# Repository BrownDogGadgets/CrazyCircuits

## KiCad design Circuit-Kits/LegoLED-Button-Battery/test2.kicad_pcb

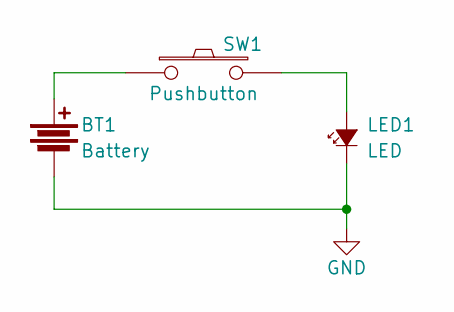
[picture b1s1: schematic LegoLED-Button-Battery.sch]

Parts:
BT1: Battery; CR2032-3x3-NO-ROTATE
LED1: LED; LED-5MMD-2.5MMP-2x2
SW1: Pushbutton; BUTTON-1x3-TH-OMRON-B3F-1XXX

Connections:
GND: BT1.GND, LED1.-
unnamed: BT1.+, SW1.1
unnamed: LED1.+, SW1.2

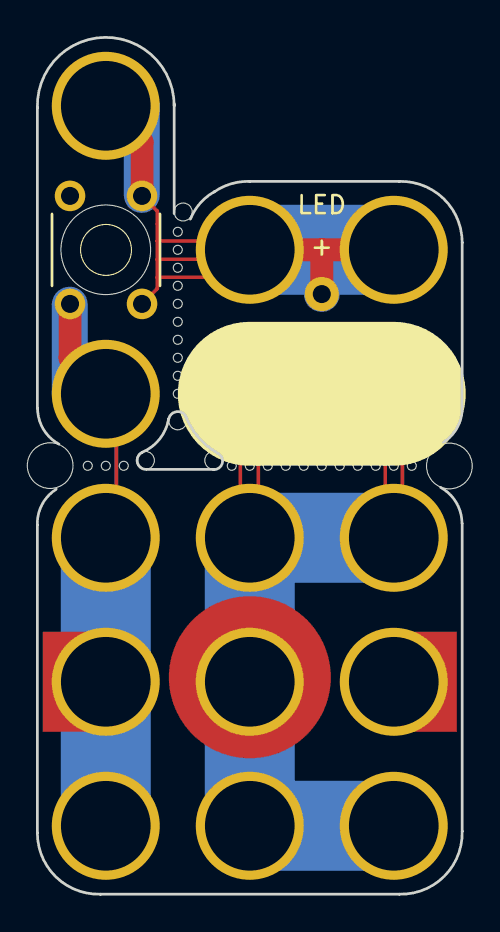
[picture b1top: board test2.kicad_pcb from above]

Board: 2 copper layers, 23.6 x 47.6 mm, 3 parts (0 on the bottom side), 3 nets.

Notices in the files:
Circuit-Kits/LegoLED-Button-Battery/LegoLED-Button-Battery.sch:
All Rights Reserved
